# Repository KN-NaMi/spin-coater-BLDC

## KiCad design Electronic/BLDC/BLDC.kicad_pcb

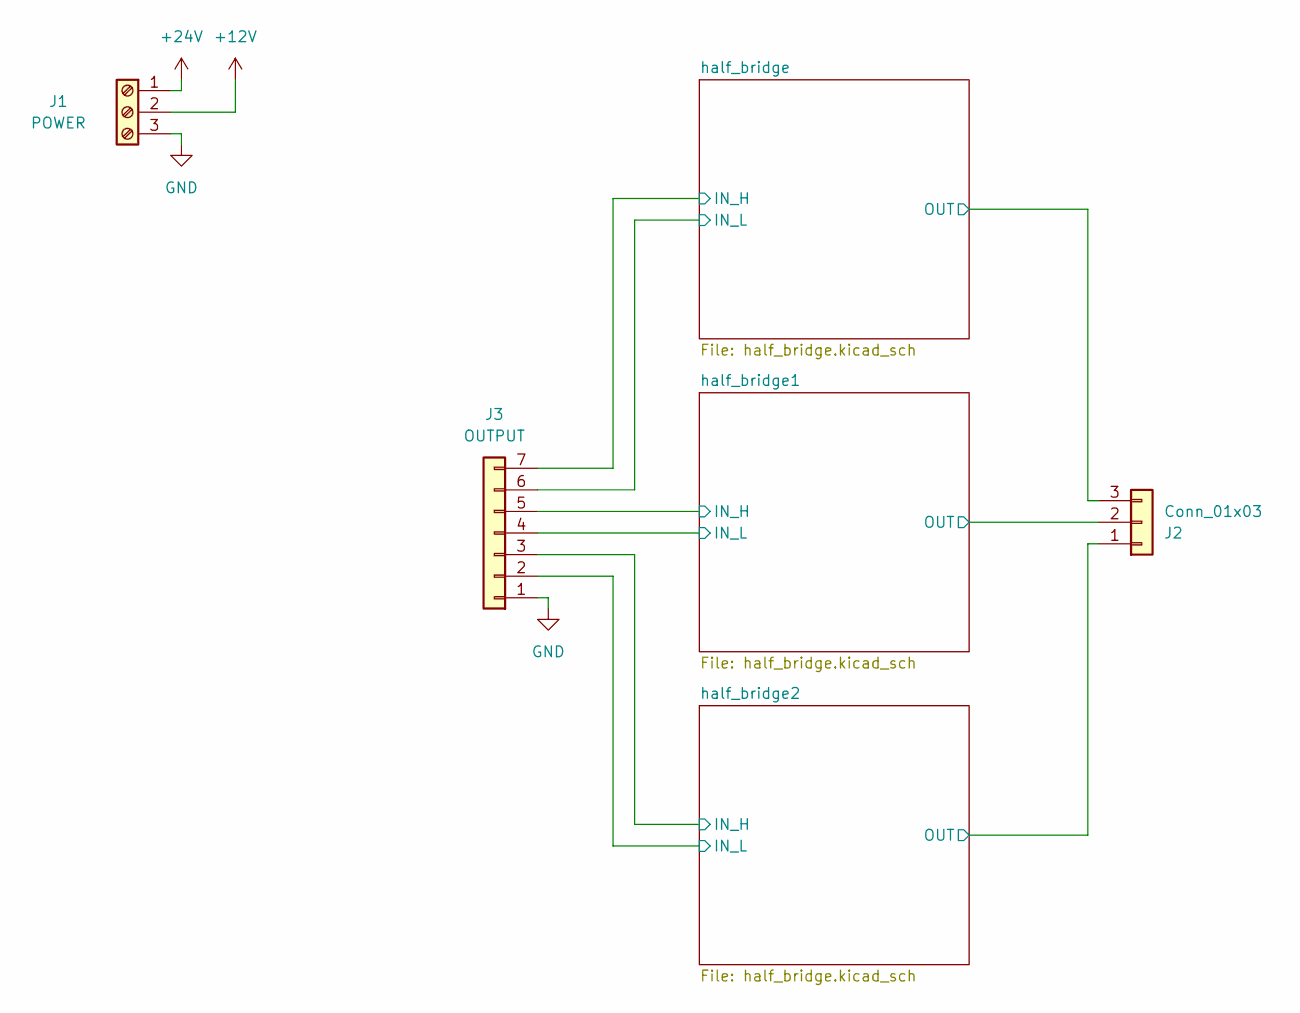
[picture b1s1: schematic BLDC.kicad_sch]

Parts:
J1: POWER; TerminalBlock_RND_205-00013_1x03_P5.00mm_Horizontal
J2: Conn_01x03; PhoenixContact_MC_1,5_3-G-3.81_1x03_P3.81mm_Horizontal
J3: OUTPUT; JST_XH_B7B-XH-A_1x07_P2.50mm_Vertical

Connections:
+12V: J1.2; also elsewhere on the board
+24V: J1.1; also elsewhere on the board
/half_bridge1/IN_H: J3.5; also elsewhere on the board
/half_bridge1/IN_L: J3.4; also elsewhere on the board
/half_bridge1/OUT: J2.2; also elsewhere on the board
/half_bridge2/IN_H: J3.3; also elsewhere on the board
/half_bridge2/IN_L: J3.2; also elsewhere on the board
/half_bridge2/OUT: J2.1; also elsewhere on the board
/half_bridge/IN_H: J3.7; also elsewhere on the board
/half_bridge/IN_L: J3.6; also elsewhere on the board
/half_bridge/OUT: J2.3; also elsewhere on the board
GND: J1.3, J3.1; also elsewhere on the board

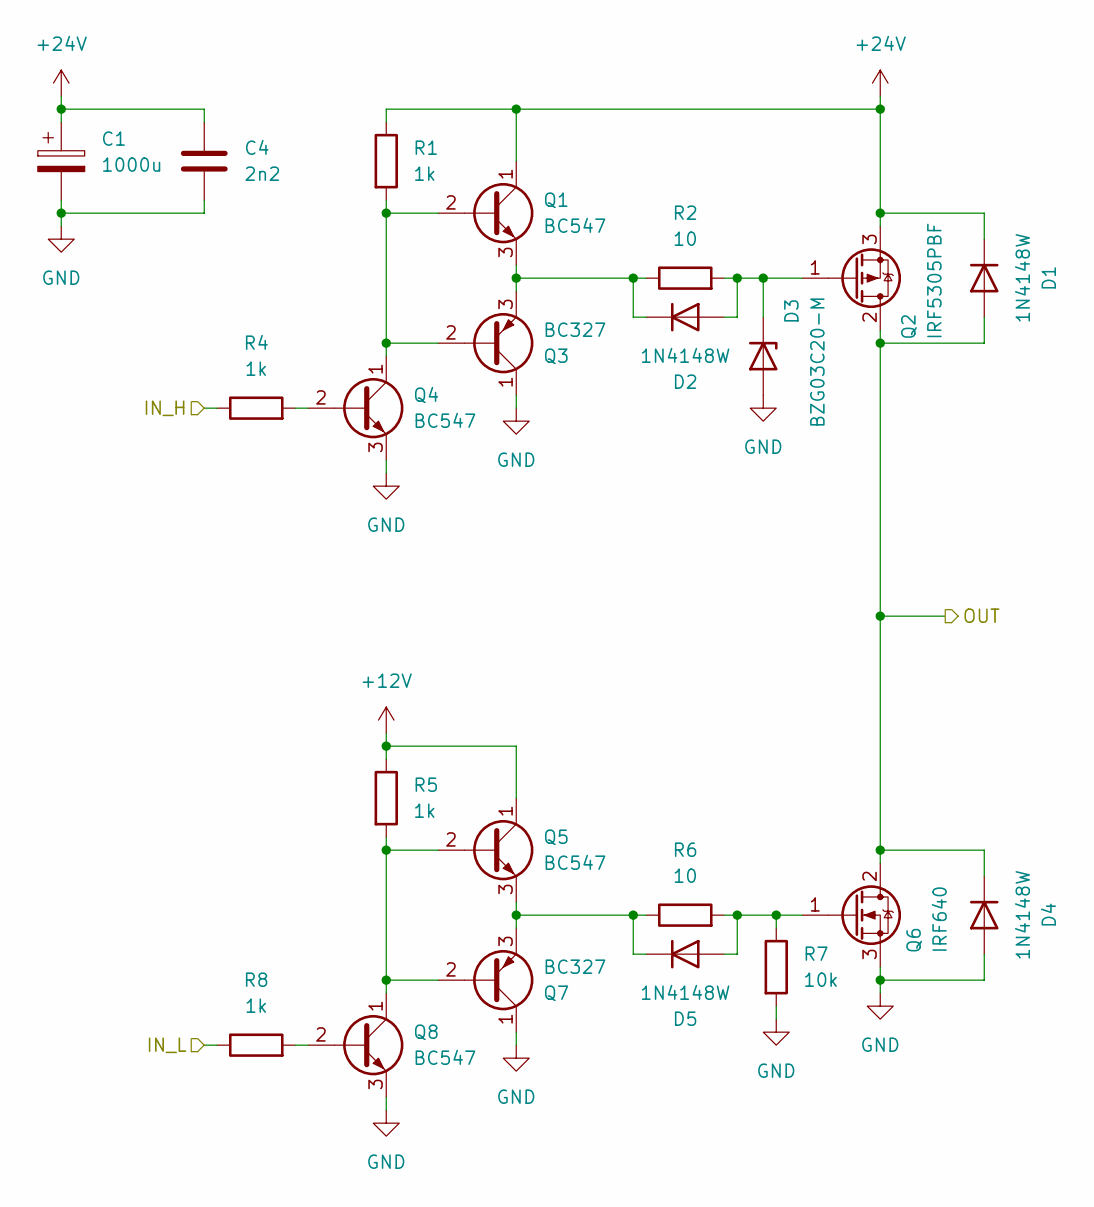
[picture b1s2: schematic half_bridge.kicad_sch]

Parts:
C1: 1000u; CP_Radial_D13.0mm_P5.00mm
C4: 2n2; C_1206_3216Metric_Pad1.33x1.80mm_HandSolder
D1, D4: 1N4148W; D_SMA-SMB_Universal_Handsoldering
D2, D5: 1N4148W; D_SOD-123
D3: BZG03C20-M; D_SMA_Handsoldering
Q1, Q4, Q5, Q8: BC547; TO-92_HandSolder
Q2: IRF5305PBF; TO-220-3_Vertical
Q3, Q7: BC327; TO-92_HandSolder
Q6: IRF640; TO-220-3_Vertical
R1, R4, R5, R8: 1k; R_0805_2012Metric
R2, R6: 10; R_0805_2012Metric
R7: 10k; R_0805_2012Metric

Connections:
+12V: Q5.1 (C), R5.1; also elsewhere on the board
+24V: C1.1, C4.1, D1.1 (K), Q1.1 (C), Q2.3 (S), R1.1; also elsewhere on the board
/half_bridge/IN_H: R4.1; also elsewhere on the board
/half_bridge/IN_L: R8.1; also elsewhere on the board
/half_bridge/OUT: D1.2 (A), D4.1 (K), Q2.2 (D), Q6.2 (D); also elsewhere on the board
GND: C1.2, C4.2, D3.2 (A), D4.2 (A), Q3.1 (C), Q4.3 (E), Q6.3 (S), Q7.1 (C), Q8.3 (E), R7.2; also elsewhere on the board
unnamed: D2.2 (A), D3.1 (K), Q2.1 (G), R2.2
unnamed: D2.1 (K), Q1.3 (E), Q3.3 (E), R2.1
unnamed: D5.2 (A), Q6.1 (G), R6.2, R7.1
unnamed: D5.1 (K), Q5.3 (E), Q7.3 (E), R6.1
unnamed: Q1.2 (B), Q3.2 (B), Q4.1 (C), R1.2
unnamed: Q4.2 (B), R4.2
unnamed: Q5.2 (B), Q7.2 (B), Q8.1 (C), R5.2
unnamed: Q8.2 (B), R8.2

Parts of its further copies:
C2, C3: 1000u; CP_Radial_D13.0mm_P5.00mm
C5, C6: 2n2; C_1206_3216Metric_Pad1.33x1.80mm_HandSolder
D6, D9, D11, D14: 1N4148W; D_SMA-SMB_Universal_Handsoldering
D7, D10, D12, D15: 1N4148W; D_SOD-123
D8, D13: BZG03C20-M; D_SMA_Handsoldering
Q9, Q12, Q13, Q16, Q17, Q20, Q21, Q24: BC547; TO-92_HandSolder
Q10, Q18: IRF5305PBF; TO-220-3_Vertical
Q11, Q15, Q19, Q23: BC327; TO-92_HandSolder
Q14, Q22: IRF640; TO-220-3_Vertical
R9, R12, R13, R16, R17, R20, R21, R24: 1k; R_0805_2012Metric
R10, R14, R18, R22: 10; R_0805_2012Metric
R15, R23: 10k; R_0805_2012Metric

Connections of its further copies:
+12V: Q13.1 (C), Q21.1 (C), R13.1, R21.1; also elsewhere on the board
+24V: C2.1, C3.1, C5.1, C6.1, D6.1 (K), D11.1 (K), Q9.1 (C), Q10.3 (S), Q17.1 (C), Q18.3 (S), R9.1, R17.1; also elsewhere on the board
/half_bridge1/IN_H: R12.1; also elsewhere on the board
/half_bridge1/IN_L: R16.1; also elsewhere on the board
/half_bridge1/OUT: D6.2 (A), D9.1 (K), Q10.2 (D), Q14.2 (D); also elsewhere on the board
/half_bridge2/IN_H: R20.1; also elsewhere on the board
/half_bridge2/IN_L: R24.1; also elsewhere on the board
/half_bridge2/OUT: D11.2 (A), D14.1 (K), Q18.2 (D), Q22.2 (D); also elsewhere on the board
GND: C2.2, C3.2, C5.2, C6.2, D8.2 (A), D9.2 (A), D13.2 (A), D14.2 (A), Q11.1 (C), Q12.3 (E), Q14.3 (S), Q15.1 (C), Q16.3 (E), Q19.1 (C), Q20.3 (E), Q22.3 (S), Q23.1 (C), Q24.3 (E), R15.2, R23.2; also elsewhere on the board
unnamed: D7.2 (A), D8.1 (K), Q10.1 (G), R10.2
unnamed: D7.1 (K), Q9.3 (E), Q11.3 (E), R10.1
unnamed: D10.2 (A), Q14.1 (G), R14.2, R15.1
unnamed: D10.1 (K), Q13.3 (E), Q15.3 (E), R14.1
unnamed: D12.2 (A), D13.1 (K), Q18.1 (G), R18.2
unnamed: D12.1 (K), Q17.3 (E), Q19.3 (E), R18.1
unnamed: D15.2 (A), Q22.1 (G), R22.2, R23.1
unnamed: D15.1 (K), Q21.3 (E), Q23.3 (E), R22.1
unnamed: Q9.2 (B), Q11.2 (B), Q12.1 (C), R9.2
unnamed: Q12.2 (B), R12.2
unnamed: Q13.2 (B), Q15.2 (B), Q16.1 (C), R13.2
unnamed: Q16.2 (B), R16.2
unnamed: Q17.2 (B), Q19.2 (B), Q20.1 (C), R17.2
unnamed: Q20.2 (B), R20.2
unnamed: Q21.2 (B), Q23.2 (B), Q24.1 (C), R21.2
unnamed: Q24.2 (B), R24.2

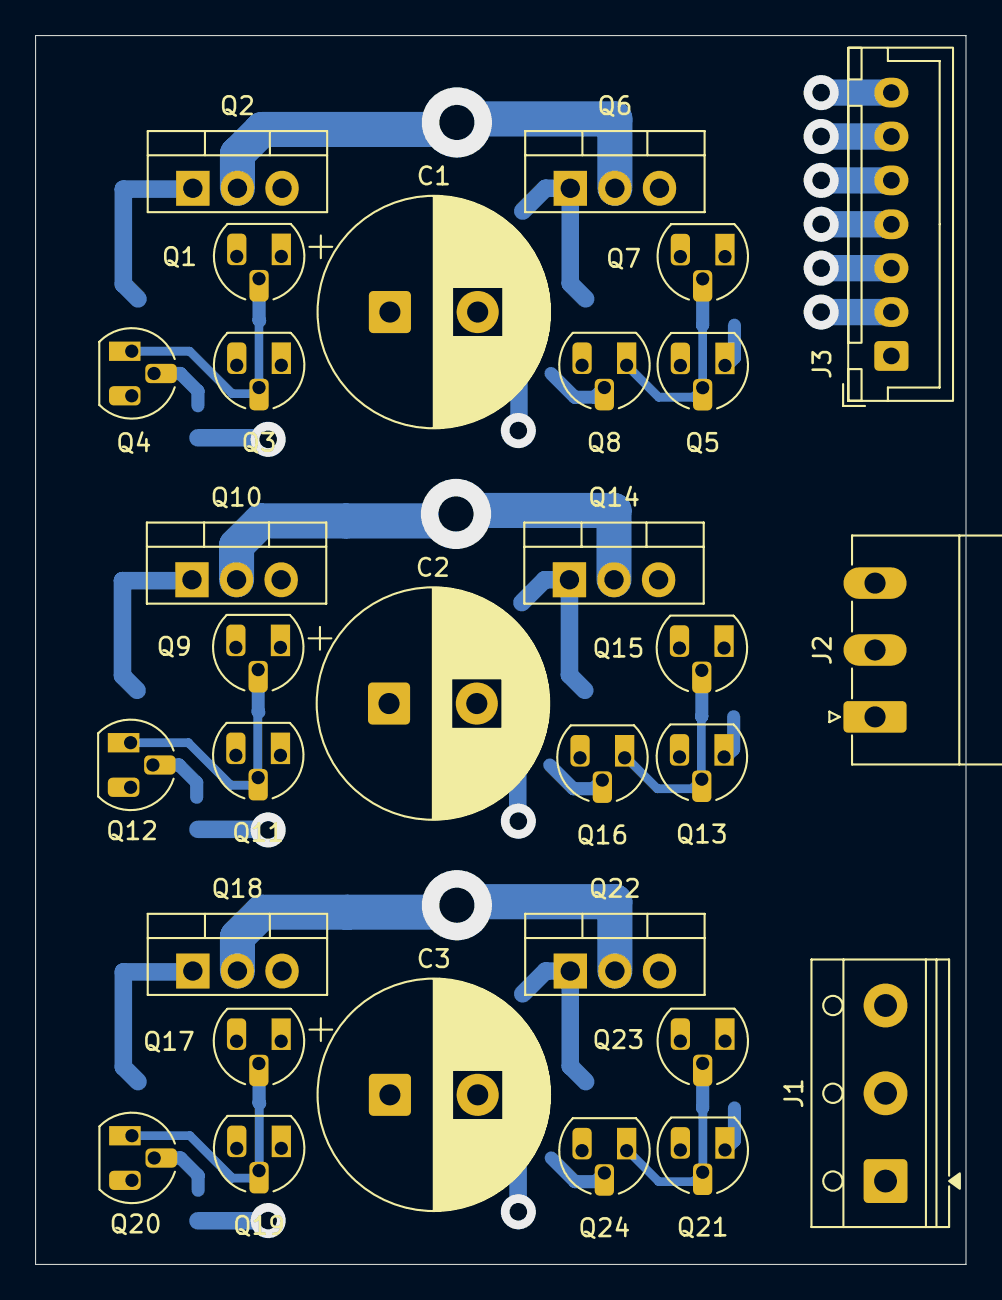
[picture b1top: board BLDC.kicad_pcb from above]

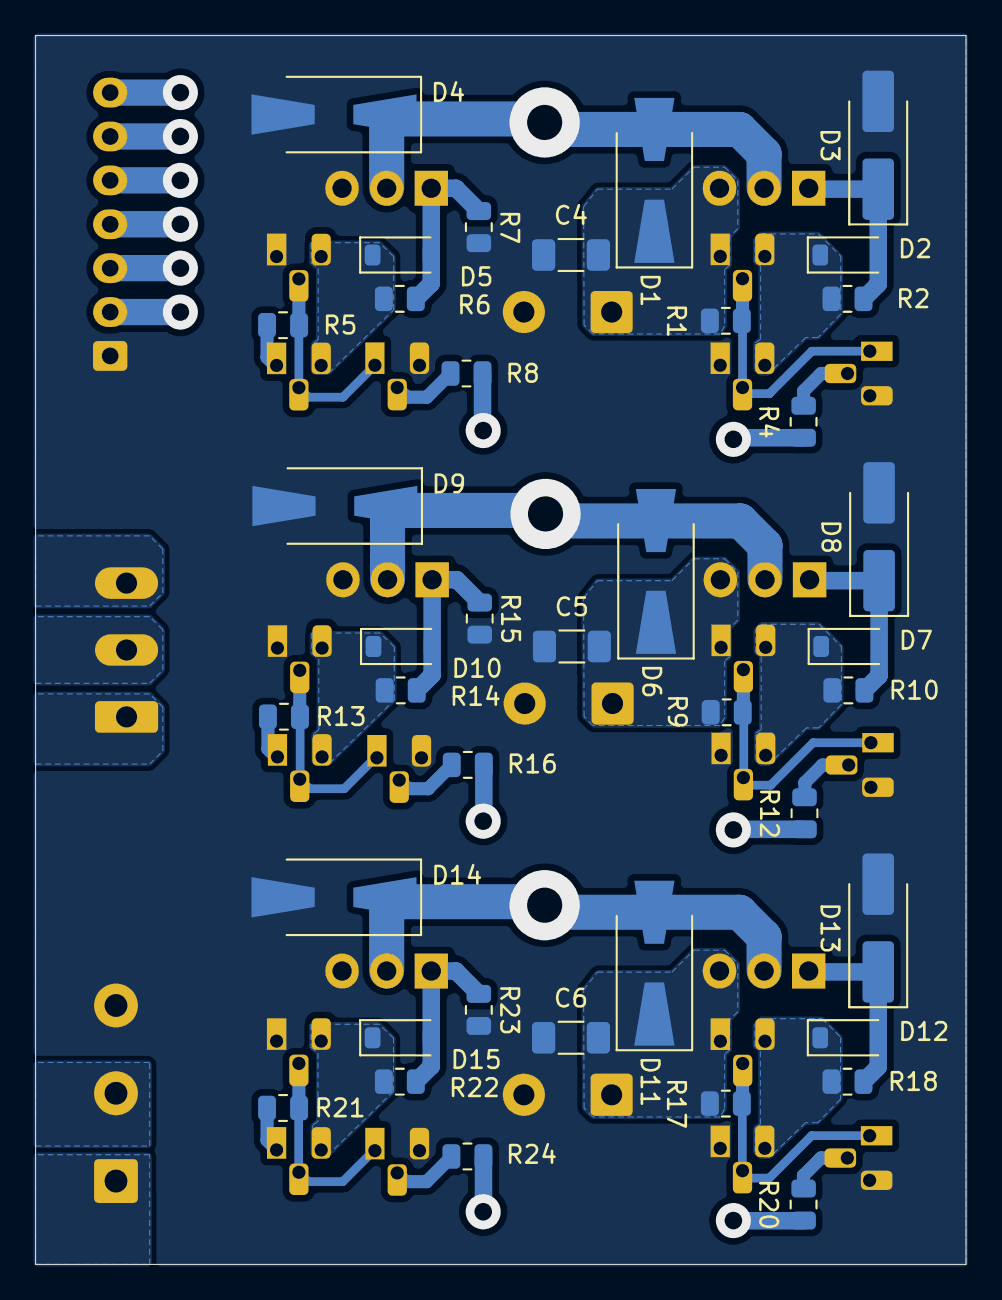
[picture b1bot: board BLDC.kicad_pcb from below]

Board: 2 copper layers, 53.0 x 70.0 mm, 69 parts (39 on the bottom side), 36 nets.

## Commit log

2026-04-24 add filse
2026-04-25 add ibom.html
2026-04-27 nc files for driling added
2026-04-30 testowy kod dla atmega328p added
